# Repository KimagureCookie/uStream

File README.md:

### WIP (I'm working on the software side of things right now!)

A few weeks ago, I wanted to buy a hot air station for some smd rework. While I was searchig for one, I came across a lot of chinese hot air stations which seem to be dirt cheap and also resonably reliable. Howerver the problem is that, these seem to be outdated design and somewhat lack in saftey!
On the other hand the offerings from top players like JBC and Wellers seems to be out of reach for any hobbyist.

I guess these are enough excuses for making my own hot air station. Since I can't make the core components (The Heater and air pump units) I will be working on the controller unit. The heater and pumps can be purchased easily through any online repair parts sellers or even better if you could directly buy from chinese sites like aliexpress. 

I will try to add everything I have cooked so far in the coming days.

Edit: As of now everthing on hardware is tested and corrected in schematics/PCB. The idea of implementing the thermocouple amplifier using an precision op-amp has to be scractched since, I can't figure out the problem with my current setup (glad I implemented the MAX6675 as a backup!).
Although I have run basic software tests, there is still more code to test thoroughly.

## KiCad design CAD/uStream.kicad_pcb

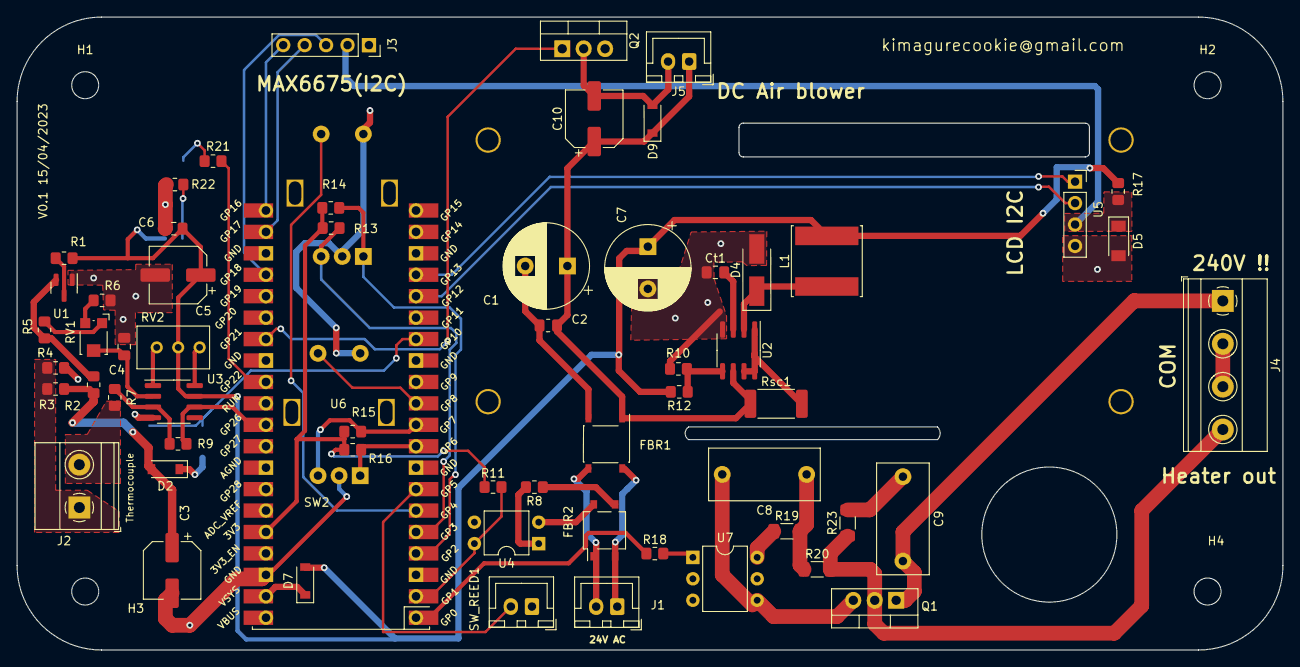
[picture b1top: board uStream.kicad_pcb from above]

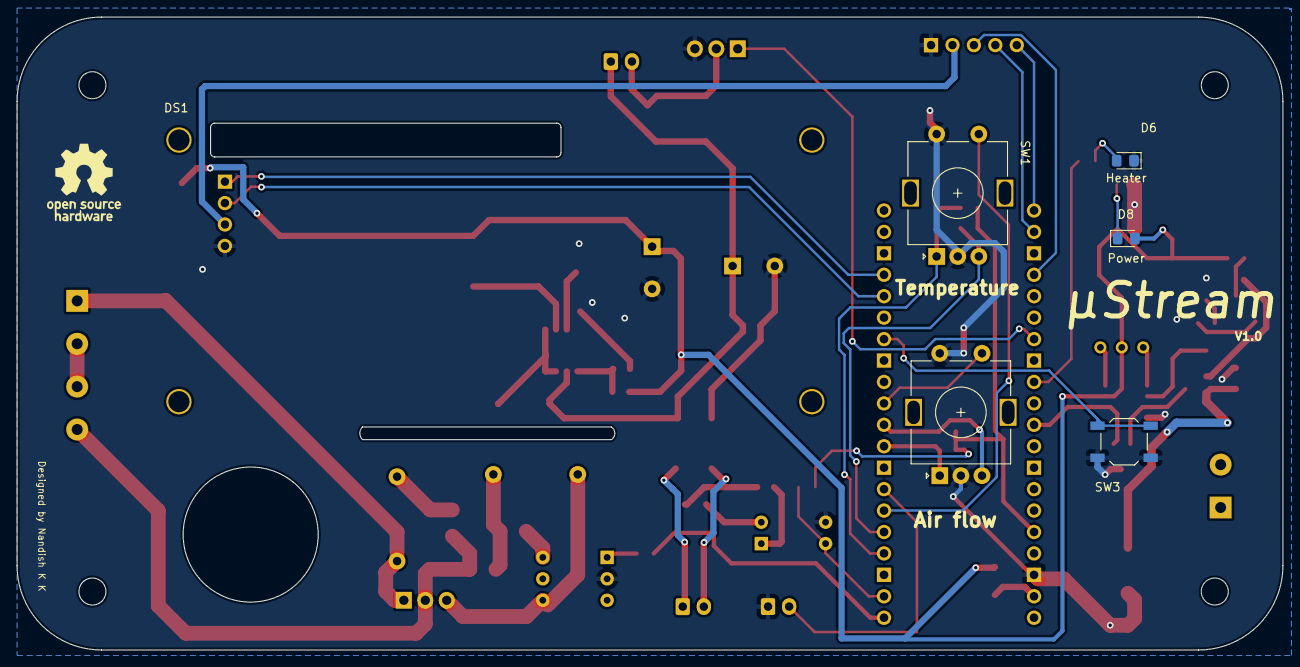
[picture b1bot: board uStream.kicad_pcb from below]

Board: 2 copper layers, 150.0 x 75.0 mm, 71 parts (7 on the bottom side), 55 nets.

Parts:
C1: 480u; CP_Radial_D10.0mm_P5.00mm
C2, C6: 0.1u; C_0805_2012Metric_Pad1.18x1.45mm_HandSolder
C3, C5, C10: 10u; CP_Elec_6.3x5.8
C4: 10u; C_0805_2012Metric_Pad1.18x1.45mm_HandSolder
C7: 220u; CP_Radial_D10.0mm_P5.00mm
C8: 50nf; C_Rect_L13.0mm_W6.0mm_P10.00mm_FKS3_FKP3_MKS4
C9: 10nf; C_Rect_L13.0mm_W6.0mm_P10.00mm_FKS3_FKP3_MKS4
Ct1: 260p; C_0805_2012Metric_Pad1.18x1.45mm_HandSolder
D2, D7, D9: 1N4148; D_SOD-123
D4: 1N5819; D_SMA_Handsoldering
D5: BZV55C4V7; D_MiniMELF
D6, D8: LED; LED_0805_2012Metric_Pad1.15x1.40mm_HandSolder
DS1: WC1602A
FBR1: ABS10; Diode_Bridge_Diotec_ABS
FBR2: RMB4S; TO-269AA
G: LOGO
H1, H2, H3, H4: MountingHole_3.2mm_M3
J1: Transformer_In; JST_XH_B2B-XH-A_1x02_P2.50mm_Vertical
J2: Thermocouple junction; TerminalBlock_Phoenix_MKDS-1,5-2-5.08_1x02_P5.08mm_Horizont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
J3: MAX6675; PinSocket_1x05_P2.54mm_Vertical
J4: Mains+Heater; TerminalBlock_Phoenix_MKDS-1,5-4-5.08_1x04_P5.08mm_Horizont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
J5: Air Blower; JST_XH_B2B-XH-A_1x02_P2.50mm_Vertical
L1: 68u; L_Sunlord_SWPA80xxS
Q1: BTA16-600B; TO-220-3_Vertical
Q2: STP55NF06; TO-220-3_Vertical
R1, R7, R22: 1k; R_0805_2012Metric_Pad1.20x1.40mm_HandSolder
R2: 47k; R_0805_2012Metric_Pad1.20x1.40mm_HandSolder
R3: 6.8k; R_0805_2012Metric_Pad1.20x1.40mm_HandSolder
R4: 110; R_0805_2012Metric_Pad1.20x1.40mm_HandSolder
R5: 102k; R_0805_2012Metric_Pad1.20x1.40mm_HandSolder
R6: 50; R_0805_2012Metric_Pad1.20x1.40mm_HandSolder
R8: 2k; R_0805_2012Metric_Pad1.20x1.40mm_HandSolder
R9: 43k; R_0805_2012Metric_Pad1.20x1.40mm_HandSolder
R10: 2.4k; R_0805_2012Metric_Pad1.20x1.40mm_HandSolder
R11: 1.5k; R_0805_2012Metric_Pad1.20x1.40mm_HandSolder
R12: 9.1k; R_0805_2012Metric_Pad1.20x1.40mm_HandSolder
R13, R14, R15, R16: 10k; R_0805_2012Metric_Pad1.20x1.40mm_HandSolder
R17: 51; R_0805_2012Metric_Pad1.20x1.40mm_HandSolder
R18: 510; R_0805_2012Metric_Pad1.20x1.40mm_HandSolder
R19: 360; R_1206_3216Metric_Pad1.30x1.75mm_HandSolder
R20: 680; R_1206_3216Metric_Pad1.30x1.75mm_HandSolder
R21: 360; R_0805_2012Metric_Pad1.20x1.40mm_HandSolder
R23: 39; R_1206_3216Metric_Pad1.30x1.75mm_HandSolder
RV1: 100; Potentiometer_Bourns_TC33X_Vertical
RV2: 20k; Potentiometer_Bourns_3296W_Vertical
Rsc1: 0.3; R_2512_6332Metric_Pad1.40x3.35mm_HandSolder
SW1: Heater Encoder; RotaryEncoder_Alps_EC11E-Switch_Vertical_H20mm
SW2: Control for Air blower; RotaryEncoder_Alps_EC11E-Switch_Vertical_H20mm
SW3: SW_SPST; SW_SPST_TL3342
SW_REED1: SW_Reed; JST_XH_B2B-XH-A_1x02_P2.50mm_Vertical
U1: TL431DBZ; SOT-23
U2: MC34063AD; SOIC-8_3.9x4.9mm_P1.27mm
U3: OP07; SOIC-8_3.9x4.9mm_P1.27mm
U4: PC817; DIP-4_W7.62mm
U5: EA_T123X-I2C; PinSocket_1x04_P2.54mm_Vertical
U6: Pico; RPi_Pico_SMD_TH
U7: MOC3022M; DIP-6_W7.62mm

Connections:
3.3V: R11.1, R13.2, R14.2, R15.2, R16.2, U6.36 (3V3)
6Vdc: C5.1, C6.2, C7.1, D7.2 (A), D8.2 (A), L1.2, R1.2, R12.2, R17.1, RV2.2, U3.7 (V+)
22.8v: C1.1, C2.2, C10.1, D9.1 (K), FBR1.1 (+), J5.1, Rsc1.1, U2.6 (Vin)
/4.7V: D5.1 (K), J3.2, R17.2, U5.3 (VSS)
/CLK1: R14.1, SW1.A, U6.4 (GPIO2)
/CLK2: R16.1, SW2.A, U6.9 (GPIO6)
/COLD: C9.2, J4.1, Q1.1 (A1)
/CS: J3.4, U6.22 (GPIO17)
/DT1: R13.1, SW1.B, U6.5 (GPIO3)
/DT2: R15.1, SW2.B, U6.10 (GPIO7)
/Hot: J4.4, Q1.2 (A2), R20.2, R23.1
/SCK: J3.3, U6.24 (GPIO18)
/SO: J3.5, U6.21 (GPIO16)
/SW1: SW1.S1, U6.6 (GPIO4)
/SW3: SW2.S1, U6.11 (GPIO8)
/T+: J2.1, R3.1, R4.2
/T-: J2.2, R7.2
/Vgs=3v: Q2.1 (G), U6.27 (GPIO21)
AC1: FBR1.4, FBR2.2, J1.1
AC2: FBR1.3, FBR2.1, J1.2
GND: C1.2, C2.1, C3.2, C4.2, C5.2, C6.1, C7.2, Ct1.1, D2.1 (K), D4.2 (A), D5.2 (A), D6.1 (K), FBR1.2 (-), J3.1, Q2.3 (S), R4.1, R6.1, R10.2, R22.2, SW1.C, SW1.S2, SW2.C, SW2.S2, SW3.1 (A), SW_REED1.1, U1.1 (K), U2.4 (GND), U3.4 (V-), U4.3, U5.4 (Ground), U6.38 (GND), U7.2
unnamed: C3.1, D2.2 (A), R2.1, R3.2
unnamed: C4.1, RV1.2, U3.2 (-)
unnamed: C8.1, R19.2, R20.1
unnamed: C8.2, Q1.3 (G), U7.4
unnamed: C9.1, R23.2
unnamed: C10.2, D9.2 (A), J5.2, Q2.2 (D)
unnamed: Ct1.2, U2.3 (TC)
unnamed: D4.1 (K), L1.1, U2.2 (SwE)
unnamed: D6.2 (A), R21.2
unnamed: D7.1 (K), U6.39 (VSYS)
unnamed: D8.1 (K), R22.1
unnamed: FBR2.3 (+), R8.1
unnamed: FBR2.4 (-), U4.2
unnamed: J4.2, J4.3
unnamed: R1.1, U1.3 (A)
unnamed: R2.2, R5.1, U1.2 (REF)
unnamed: R5.2, RV1.1
unnamed: R6.2, RV1.3
unnamed: R7.1, R9.2, U3.3 (+)
unnamed: R8.2, U4.1
unnamed: R10.1, R12.1, U2.5 (Vfb)
unnamed: R18.2, U7.1
unnamed: R19.1, U7.6
unnamed: R21.1, U6.29 (GPIO22)
unnamed: RV2.1, U3.8 (VOS)
unnamed: RV2.3, U3.1 (VOS)
unnamed: Rsc1.2, U2.1 (SwC), U2.7 (Ipk), U2.8 (DC)
unnamed: SW3.2 (B), U6.14 (GPIO10)
unnamed: SW_REED1.2, U6.7 (GPIO5)
unnamed: U5.1 (SCL), U6.17 (GPIO13)
unnamed: U5.2 (SDA), U6.16 (GPIO12)
Sense: R11.2, U4.4, U6.2 (GPIO1)
Temperature: R9.1, U3.6, U6.31 (GPIO26_ADC0)
Trigger: R18.1, U6.1 (GPIO0)

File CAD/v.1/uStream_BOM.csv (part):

"Source:","C:\Users\*****\Documents\KiCad\hot air station\uStream.kicad_sch"
"Date:","4/14/2023 2:54:58 AM"
"Tool:","Eeschema (6.0.10)"
"Generator:","C:\Program Files\KiCad\6.0\bin\scripting\plugins/bom_csv_grouped_by_value.py"
"Component Count:","70"

"Individual Components:"

"Item","Qty","Reference(s)","Value","LibPart","Footprint","Datasheet"
"","","C1","480u","Device:C_Polarized","Capacitor_THT:CP_Radial_D10.0mm_P5.00mm","~"
"","","C2","0.1u","Device:C","Capacitor_SMD:C_0805_2012Metric_Pad1.18x1.45mm_HandSolder","~"
"","","C3","10u","Device:C","Capacitor_SMD:CP_Elec_6.3x5.8","~"
"","","C4","10u","Device:C","Capacitor_SMD:C_0805_2012Metric_Pad1.18x1.45mm_HandSolder","~"
"","","C5","10u","Device:C_Polarized","Capacitor_SMD:CP_Elec_6.3x5.8","~"
"","","C6","0.1u","Device:C","Capacitor_SMD:C_0805_2012Metric_Pad1.18x1.45mm_HandSolder","~"
"","","C7","220u","Device:C_Polarized","Capacitor_THT:CP_Radial_D10.0mm_P5.00mm","~"
"","","C8","50nf","Device:C","Capacitor_THT:C_Rect_L13.0mm_W6.0mm_P10.00mm_FKS3_FKP3_MKS4","~"
"","","C9","10nf","Device:C","Capacitor_THT:C_Rect_L13.0mm_W6.0mm_P10.00mm_FKS3_FKP3_MKS4","~"
"","","C10","10u","Device:C_Polarized","Capacitor_SMD:CP_Elec_6.3x5.8","~"
"","","Ct1","260p","Device:C","Capacitor_SMD:C_0805_2012Metric_Pad1.18x1.45mm_HandSolder","~"
"","","D2","1N4148","Device:D","Diode_SMD:D_SOD-123","~"
"","","D4","1N5819","Diode:1N5819","Diode_SMD:D_SMA_Handsoldering","http://www.vishay.com/docs/88525/1n5817.pdf"
"","","D5","BZV55C4V7","Diode:BZV55C4V7","Diode_SMD:D_MiniMELF","https://assets.nexperia.com/documents/data-sheet/BZV55_SER.pdf"
"","","D6","LED","Device:LED","LED_SMD:LED_0805_2012Metric_Pad1.15x1.40mm_HandSolder","~"
"","","D7","1N4148","Diode:1N4148","Diode_SMD:D_SOD-123","https://assets.nexperia.com/documents/data-sheet/1N4148_1N4448.pdf"
"","","D8","LED","Device:LED","LED_SMD:LED_0805_2012Metric_Pad1.15x1.40mm_HandSolder","~"
"","","D9","1N4148","Device:D","Diode_SMD:D_SOD-123","~"
"","","DS1","WC1602A","Display_Character:WC1602A","Display:WC1602A","http://www.wincomlcd.com/pdf/WC1602A-SFYLYHTC06.pdf"
"","","FBR1","ABS10","Diode_Bridge:ABS10","Diode_SMD:Diode_Bridge_Diotec_ABS","https://diotec.com/tl_files/diotec/files/pdf/datasheets/abs2.pdf"
"","","FBR2","RMB4S","Diode_Bridge:RMB4S","Package_TO_SOT_SMD:TO-269AA","http://www.vishay.com/docs/88705/rmbs.pdf"
"","","H1","MountingHole","Mechanical:MountingHole","MountingHole:MountingHole_3.2mm_M3","~"
"","","H2","MountingHole","Mechanical:MountingHole","MountingHole:MountingHole_3.2mm_M3","~"
"","","H3","MountingHole","Mechanical:MountingHole","MountingHole:MountingHole_3.2mm_M3","~"
"","","H4","MountingHole","Mechanical:MountingHole","MountingHole:MountingHole_3.2mm_M3","~"
"","","J1","Transformer_In","Connector_Generic:Conn_01x02","Connector_JST:JST_XH_B2B-XH-A_1x02_P2.50mm_Vertical","~"
"","","J2","Thermocouple junction","Connector:Screw_Terminal_01x02","TerminalBlock_Phoenix:TerminalBlock_Phoenix_MKDS-1,5-2-5.08_1x02_P5.08mm_Horizontal","~"
"","","J3","MAX6675","Connector:Conn_01x05_Male","Connector_PinSocket_2.54mm:PinSocket_1x05_P2.54mm_Vertical","~"
"","","J4","Mains+Heater","Connector:Screw_Terminal_01x04","TerminalBlock_Phoenix:TerminalBlock_Phoenix_MKDS-1,5-4-5.08_1x04_P5.08mm_Horizontal","~"
"","","J5","Air Blower","Connector_Generic:Conn_01x02","Connector_JST:JST_XH_B2B-XH-A_1x02_P2.50mm_Vertical","~"
"","","L1","68u","Device:L","Inductor_SMD:L_Sunlord_SWPA80xxS","~"
"","","Q1","BTA16-600B","Triac_Thyristor:BTA16-600B","Package_TO_SOT_THT:TO-220-3_Vertical","https://www.st.com/resource/en/datasheet/bta16.pdf"
"","","Q2","STP55NF06","Transistor_FET:IRF540N","Package_TO_SOT_THT:TO-220-3_Vertical","http://www.irf.com/product-info/datasheets/data/irf540n.pdf"
"","","R1","1k","Device:R","Resistor_SMD:R_0805_2012Metric_Pad1.20x1.40mm_HandSolder","~"
"","","R2","47k","Device:R","Resistor_SMD:R_0805_2012Metric_Pad1.20x1.40mm_HandSolder","~"
"","","R3","6.8k","Device:R","Resistor_SMD:R_0805_2012Metric_Pad1.20x1.40mm_HandSolder","~"
"","","R4","110","Device:R","Resistor_SMD:R_0805_2012Metric_Pad1.20x1.40mm_HandSolder","~"
"","","R5","102k","Device:R","Resistor_SMD:R_0805_2012Metric_Pad1.20x1.40mm_HandSolder","~"
"","","R6","50","Device:R","Resistor_SMD:R_0805_2012Metric_Pad1.20x1.40mm_HandSolder","~"
"","","R7","1k","Device:R","Resistor_SMD:R_0805_2012Metric_Pad1.20x1.40mm_HandSolder","~"
"","","R8","2k","Device:R","Resistor_SMD:R_0805_2012Metric_Pad1.20x1.40mm_HandSolder","~"
"","","R9","43k","Device:R","Resistor_SMD:R_0805_2012Metric_Pad1.20x1.40mm_HandSolder","~"
"","","R10","2.4k","Device:R","Resistor_SMD:R_0805_2012Metric_Pad1.20x1.40mm_HandSolder","~"
"","","R11","1.5k","Device:R","Resistor_SMD:R_0805_2012Metric_Pad1.20x1.40mm_HandSolder","~"
"","","R12","9.1k","Device:R","Resistor_SMD:R_0805_2012Metric_Pad1.20x1.40mm_HandSolder","~"
"","","R13","10k","Device:R","Resistor_SMD:R_0805_2012Metric_Pad1.20x1.40mm_HandSolder","~"
"","","R14","10k","Device:R","Resistor_SMD:R_0805_2012Metric_Pad1.20x1.40mm_HandSolder","~"
"","","R15","10k","Device:R","Resistor_SMD:R_0805_2012Metric_Pad1.20x1.40mm_HandSolder","~"
"","","R16","10k","Device:R","Resistor_SMD:R_0805_2012Metric_Pad1.20x1.40mm_HandSolder","~"
"","","R17","51","Device:R","Resistor_SMD:R_0805_2012Metric_Pad1.20x1.40mm_HandSolder","~"
"","","R18","510","Device:R","Resistor_SMD:R_0805_2012Metric_Pad1.20x1.40mm_HandSolder","~"
"","","R19","360","Device:R","Resistor_SMD:R_1206_3216Metric_Pad1.30x1.75mm_HandSolder","~"
"","","R20","680","Device:R","Resistor_SMD:R_1206_3216Metric_Pad1.30x1.75mm_HandSolder","~"
"","","R21","360","Device:R","Resistor_SMD:R_0805_2012Metric_Pad1.20x1.40mm_HandSolder","~"
"","","R22","1k","Device:R","Resistor_SMD:R_0805_2012Metric_Pad1.20x1.40mm_HandSolder","~"
"","","R23","39","Device:R","Resistor_SMD:R_1206_3216Metric_Pad1.30x1.75mm_HandSolder","~"
"","","Rsc1","0.3","Device:R","Resistor_SMD:R_2512_6332Metric_Pad1.40x3.35mm_HandSolder","~"
"","","RV1","100","Device:R_Potentiometer","Potentiometer_SMD:Potentiometer_Bourns_TC33X_Vertical","~"
"","","RV2","20k","Device:R_Potentiometer","Potentiometer_THT:Potentiometer_Bourns_3296W_Vertical","~"
"","","SW1","Heater Encoder","Device:RotaryEncoder_Switch","Rotary_Encoder:RotaryEncoder_Alps_EC11E-Switch_Vertical_H20mm","~"
"","","SW2","Control for Air blower","Device:RotaryEncoder_Switch","Rotary_Encoder:RotaryEncoder_Alps_EC11E-Switch_Vertical_H20mm","~"
"","","SW3","SW_SPST","Switch:SW_SPST","Button_Switch_SMD:SW_SPST_TL3342","~"
"","","SW_REED1","SW_Reed","Switch:SW_Reed","Connector_JST:JST_XH_B2B-XH-A_1x02_P2.50mm_Vertical","~"
"","","U1","TL431DBZ","Reference_Voltage:TL431DBZ","Package_TO_SOT_SMD:SOT-23","http://www.ti.com/lit/ds/symlink/tl431.pdf"
"","","U2","MC34063AD","Regulator_Switching:MC34063AD","Package_SO:SOIC-8_3.9x4.9mm_P1.27mm","http://www.onsemi.com/pub_link/Collateral/MC34063A-D.PDF"
"","","U3","OP07","Amplifier_Operational:OP07","Package_SO:SOIC-8_3.9x4.9mm_P1.27mm","https://www.analog.com/media/en/technical-documentation/data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"
"","","U4","PC817","Isolator:PC817","Package_DIP:DIP-4_W7.62mm","http://www.soselectronic.cz/a_info/resource/d/pc817.pdf"
"","","U5","EA_T123X-I2C","Display_Character:EA_T123X-I2C","Connector_PinSocket_2.54mm:PinSocket_1x04_P2.54mm_Vertical","http://www.lcd-module.de/pdf/doma/t123-i2c.pdf"
"","","U6","Pico","MCU_RaspberryPi_and_Boards:Pico","raspberry pi:RPi_Pico_SMD_TH",""
"","","U7","MOC3022M","Relay_SolidState:MOC3022M","Package_DIP:DIP-6_W7.62mm","https://www.onsemi.com/pub/Collateral/MOC3023M-D.PDF"



"Collated Components:"

"Item","Qty","Reference(s)","Value","LibPart","Footprint","Datasheet"
"1","1","C1","480u","Device:C_Polarized","Capacitor_THT:CP_Radial_D10.0mm_P5.00mm","~"
"2","2","C2, C6","0.1u","Device:C","Capacitor_SMD:C_0805_2012Metric_Pad1.18x1.45mm_HandSolder","~"
"3","1","C3","10u","Device:C","Capacitor_SMD:CP_Elec_6.3x5.8","~"
"4","1","C4","10u","Device:C","Capacitor_SMD:C_0805_2012Metric_Pad1.18x1.45mm_HandSolder","~"
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
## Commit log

2023-04-13 micro_stream_commit
2023-04-29 CAD files added
2023-04-29 reorganized
2023-05-05 v0.2
2023-05-06 schematic and pcb updated
2023-05-07 pictures added
